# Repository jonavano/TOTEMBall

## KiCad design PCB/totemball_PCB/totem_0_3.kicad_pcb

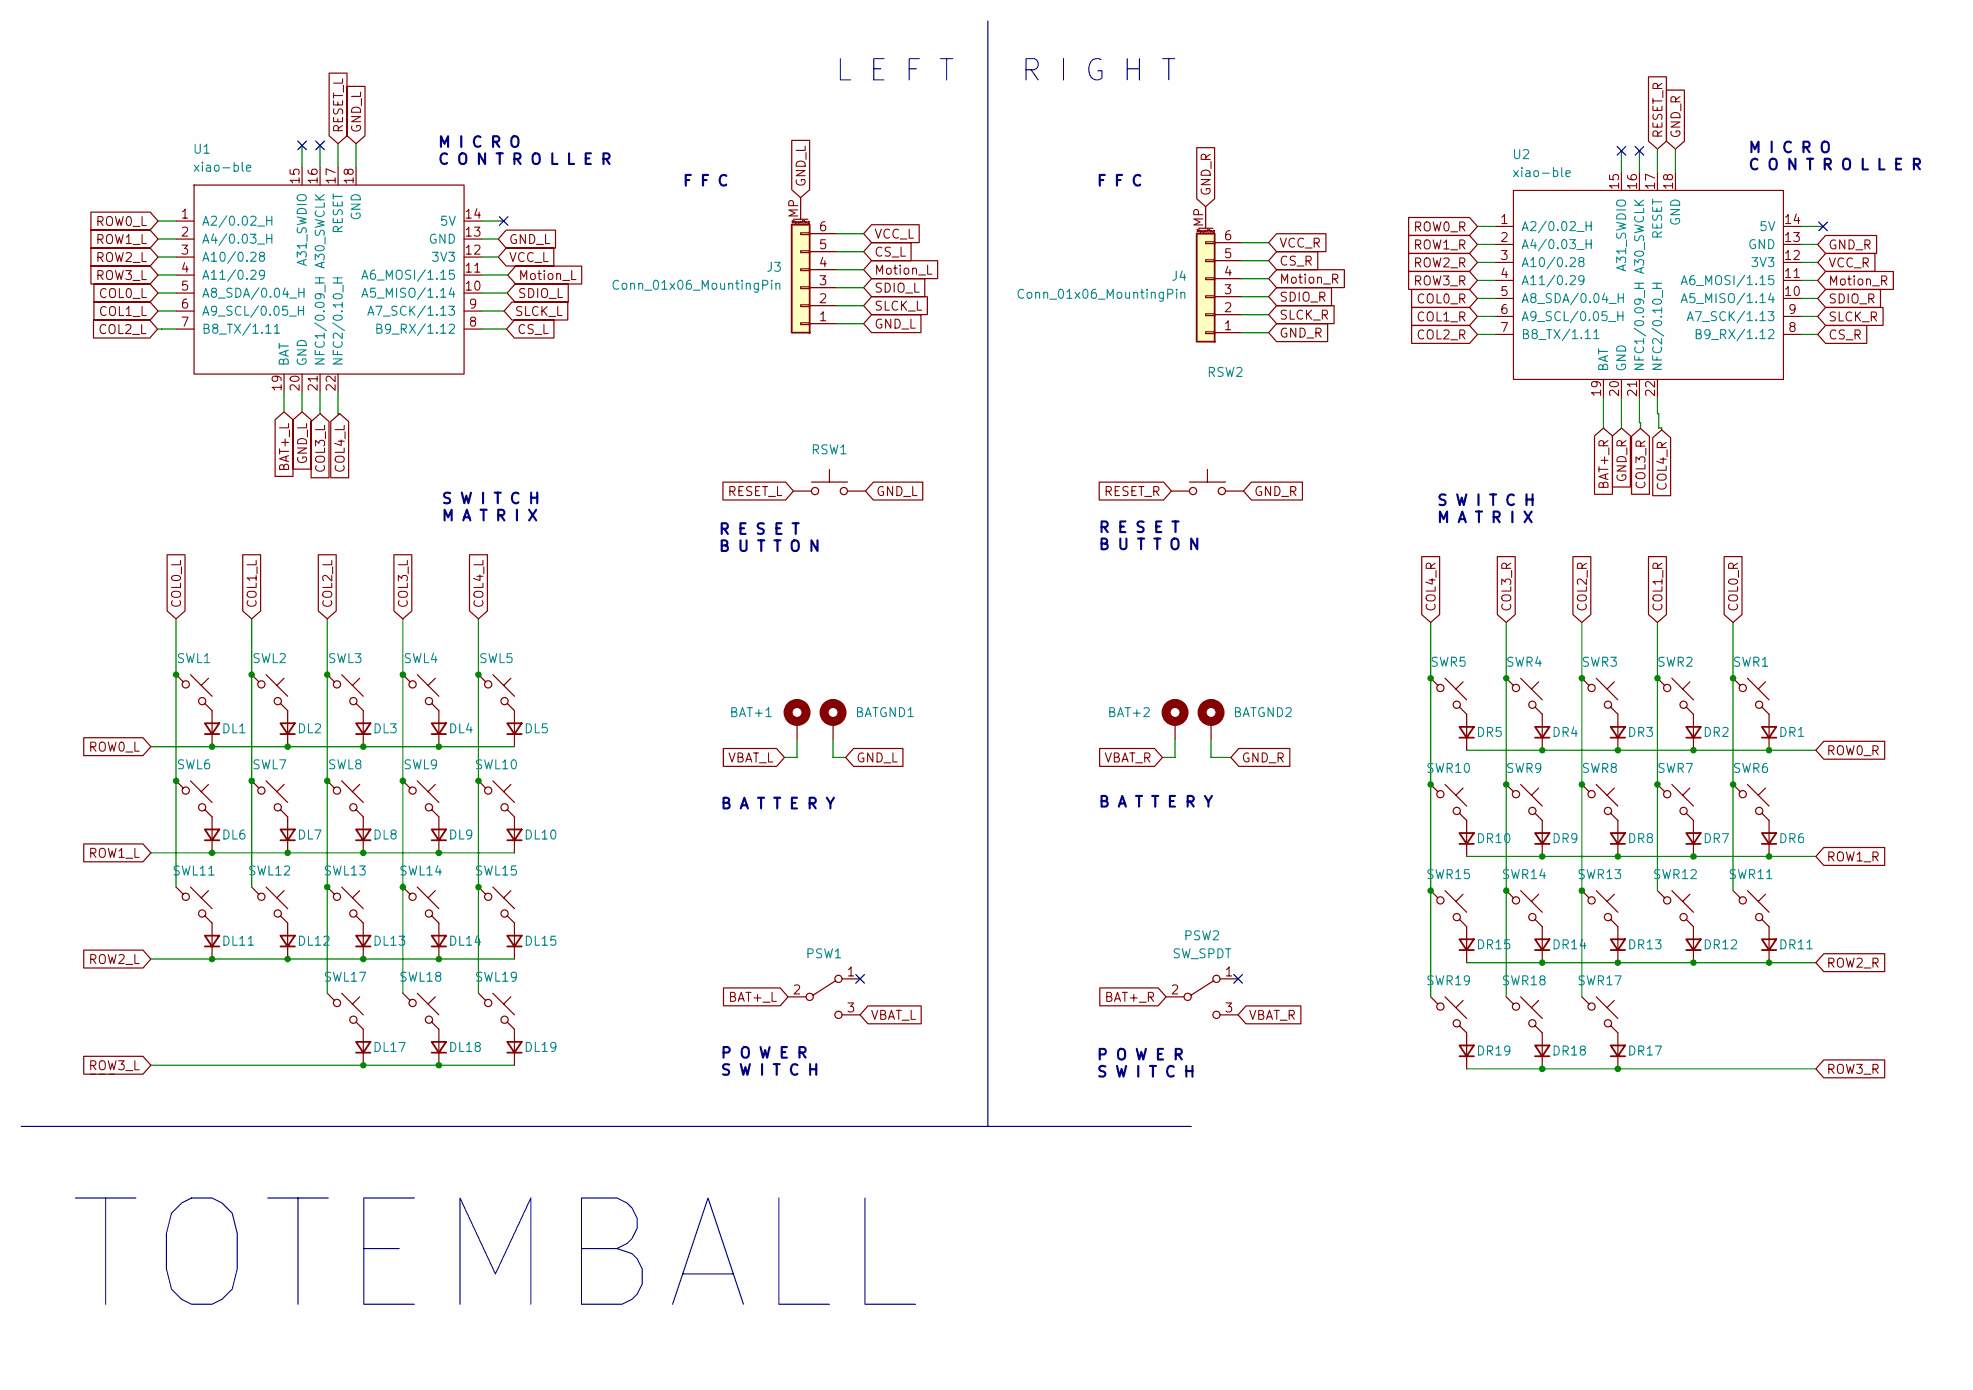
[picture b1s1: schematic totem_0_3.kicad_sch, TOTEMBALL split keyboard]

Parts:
BAT+1, BAT+2: +; BatteryPad
BATGND1, BATGND2: -; BatteryPad
DL1, DL2, DL3, DL4, DL5, DL6, DL7, DL8, DL9, DL10, DL11, DL12, DL13, DL14, DL15, DL17, DL18, DL19: D_Small; Diode_SOD123
DR1, DR2, DR3, DR4, DR5, DR6, DR7, DR8, DR9, DR10, DR11, DR12, DR13, DR14, DR15, DR17, DR18, DR19: D_Small; Diode_SOD123
J3, J4: Conn_01x06_MountingPin; GT-F0501SR10-06S1101
PSW1, PSW2: SW_SPDT; MSK12C02
RSW1, RSW2: SW_Push; SKHLLCA010
SWL1, SWL2, SWL3, SWL4, SWL5, SWL6, SWL7, SWL8, SWL9, SWL10, SWL11, SWL12, SWL13, SWL14, SWL15, SWL17, SWL18, SWL19: SW_Push_45deg; SW_Kailh_Choc_V1V2_HotSwap_Hybrid
SWR1, SWR2, SWR3, SWR4, SWR5, SWR6, SWR7, SWR8, SWR9, SWR10, SWR11, SWR12, SWR13, SWR14, SWR15, SWR17, SWR18, SWR19: SW_Push_45deg; SW_Kailh_Choc_V1V2_HotSwap_Hybrid
U1, U2: xiao-ble; xiao-ble-smd-cutout

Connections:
BAT+_L: PSW1.2 (B), U1.19 (BAT)
BAT+_R: PSW2.2 (B), U2.19 (BAT)
COL0_L: SWL1.1, SWL6.1, SWL11.1, U1.5 (A8_SDA/0.04_H)
COL0_R: SWR1.1, SWR6.1, SWR11.1, U2.5 (A8_SDA/0.04_H)
COL1_L: SWL2.1, SWL7.1, SWL12.1, U1.6 (A9_SCL/0.05_H)
COL1_R: SWR2.1, SWR7.1, SWR12.1, U2.6 (A9_SCL/0.05_H)
COL2_L: SWL3.1, SWL8.1, SWL13.1, SWL17.1, U1.7 (B8_TX/1.11)
COL2_R: SWR3.1, SWR8.1, SWR13.1, SWR17.1, U2.7 (B8_TX/1.11)
COL3_L: SWL4.1, SWL9.1, SWL14.1, SWL18.1, U1.21 (NFC1/0.09_H)
COL3_R: SWR4.1, SWR9.1, SWR14.1, SWR18.1, U2.21 (NFC1/0.09_H)
COL4_L: SWL5.1, SWL10.1, SWL15.1, SWL19.1, U1.22 (NFC2/0.10_H)
COL4_R: SWR5.1, SWR10.1, SWR15.1, SWR19.1, U2.22 (NFC2/0.10_H)
CS_L: J3.5, U1.8 (B9_RX/1.12)
CS_R: J4.5, U2.8 (B9_RX/1.12)
GND_L: BATGND1.1, J3.1, J3.MP (MountPin), RSW1.2, U1.13 (GND), U1.18 (GND), U1.20 (GND)
GND_R: BATGND2.1, J4.1, J4.MP (MountPin), RSW2.2, U2.13 (GND), U2.18 (GND), U2.20 (GND)
Motion_L: J3.4, U1.11 (A6_MOSI/1.15)
Motion_R: J4.4, U2.11 (A6_MOSI/1.15)
unnamed: DL1.2 (A), SWL1.2
unnamed: DL2.2 (A), SWL2.2
unnamed: DL3.2 (A), SWL3.2
unnamed: DL4.2 (A), SWL4.2
unnamed: DL5.2 (A), SWL5.2
unnamed: DL6.2 (A), SWL6.2
unnamed: DL7.2 (A), SWL7.2
unnamed: DL8.2 (A), SWL8.2
unnamed: DL9.2 (A), SWL9.2
unnamed: DL10.2 (A), SWL10.2
unnamed: DL11.2 (A), SWL11.2
unnamed: DL12.2 (A), SWL12.2
unnamed: DL13.2 (A), SWL13.2
unnamed: DL14.2 (A), SWL14.2
unnamed: DL15.2 (A), SWL15.2
unnamed: DL17.2 (A), SWL17.2
unnamed: DL18.2 (A), SWL18.2
unnamed: DL19.2 (A), SWL19.2
unnamed: DR1.2 (A), SWR1.2
unnamed: DR2.2 (A), SWR2.2
unnamed: DR3.2 (A), SWR3.2
unnamed: DR4.2 (A), SWR4.2
unnamed: DR5.2 (A), SWR5.2
unnamed: DR6.2 (A), SWR6.2
unnamed: DR7.2 (A), SWR7.2
unnamed: DR8.2 (A), SWR8.2
unnamed: DR9.2 (A), SWR9.2
unnamed: DR10.2 (A), SWR10.2
unnamed: DR11.2 (A), SWR11.2
unnamed: DR12.2 (A), SWR12.2
unnamed: DR13.2 (A), SWR13.2
unnamed: DR14.2 (A), SWR14.2
unnamed: DR15.2 (A), SWR15.2
unnamed: DR17.2 (A), SWR17.2
unnamed: DR18.2 (A), SWR18.2
unnamed: DR19.2 (A), SWR19.2
RESET_L: RSW1.1, U1.17 (RESET)
RESET_R: RSW2.1, U2.17 (RESET)
ROW0_L: DL1.1 (K), DL2.1 (K), DL3.1 (K), DL4.1 (K), DL5.1 (K), U1.1 (A2/0.02_H)
ROW0_R: DR1.1 (K), DR2.1 (K), DR3.1 (K), DR4.1 (K), DR5.1 (K), U2.1 (A2/0.02_H)
ROW1_L: DL6.1 (K), DL7.1 (K), DL8.1 (K), DL9.1 (K), DL10.1 (K), U1.2 (A4/0.03_H)
ROW1_R: DR6.1 (K), DR7.1 (K), DR8.1 (K), DR9.1 (K), DR10.1 (K), U2.2 (A4/0.03_H)
ROW2_L: DL11.1 (K), DL12.1 (K), DL13.1 (K), DL14.1 (K), DL15.1 (K), U1.3 (A10/0.28)
ROW2_R: DR11.1 (K), DR12.1 (K), DR13.1 (K), DR14.1 (K), DR15.1 (K), U2.3 (A10/0.28)
ROW3_L: DL17.1 (K), DL18.1 (K), DL19.1 (K), U1.4 (A11/0.29)
ROW3_R: DR17.1 (K), DR18.1 (K), DR19.1 (K), U2.4 (A11/0.29)
SDIO_L: J3.3, U1.10 (A5_MISO/1.14)
SDIO_R: J4.3, U2.10 (A5_MISO/1.14)
SLCK_L: J3.2, U1.9 (A7_SCK/1.13)
SLCK_R: J4.2, U2.9 (A7_SCK/1.13)
VBAT_L: BAT+1.1, PSW1.3 (C)
VBAT_R: BAT+2.1, PSW2.3 (C)
VCC_L: J3.6, U1.12 (3V3)
VCC_R: J4.6, U2.12 (3V3)

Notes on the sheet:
M I C R O C O N T R O L L E R
F F C
R E S E T B U T T O N
S W I T C H M A T R I X
P O W E R S W I T C H
TOTEMBALL
B A T T E R Y
R I G H T
L E F T

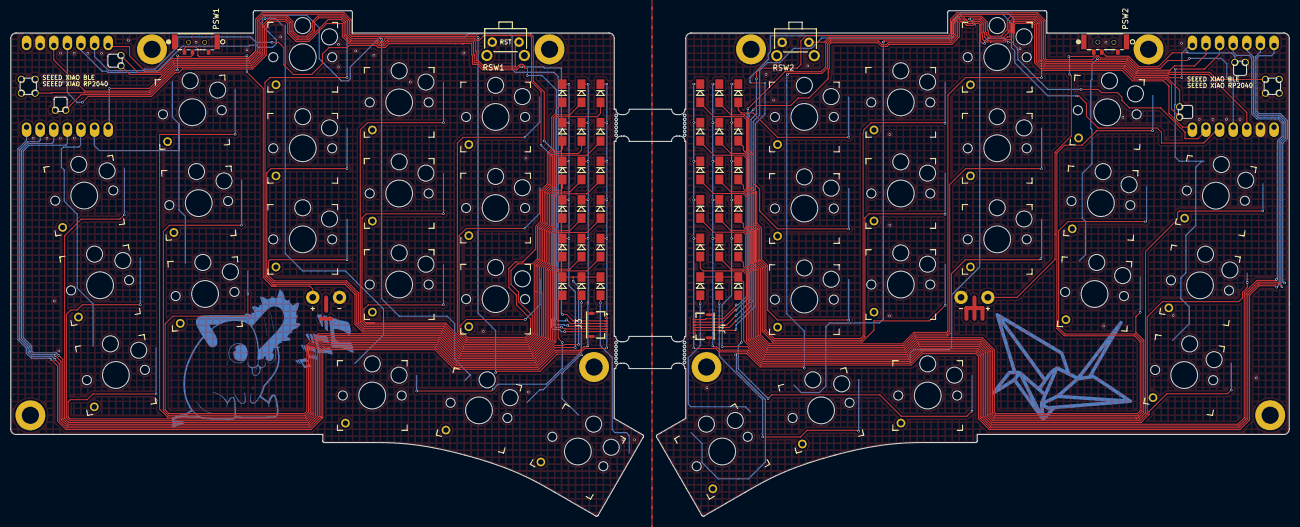
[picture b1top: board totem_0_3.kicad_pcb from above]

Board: 2 copper layers, 238.6 x 94.4 mm, 84 parts (0 on the bottom side), 72 nets.

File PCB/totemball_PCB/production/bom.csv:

Designator,Footprint,Quantity,Value,LCSC Part #
"BAT+1, BAT+2",BatteryPad,2,+,
"BATGND1, BATGND2",BatteryPad,2,-,
"DL1, DL10, DL11, DL12, DL13, DL14, DL15, DL17, DL18, DL19, DL2, DL3, DL4, DL5, DL6, DL7, DL8, DL9, DR1, DR10, DR11, DR12, DR13, DR14, DR15, DR17, DR18, DR19, DR2, DR3, DR4, DR5, DR6, DR7, DR8, DR9",Diode_SOD123,36,D_Small,
"J3, J4",GT-F0501SR10-06S1101,2,Conn_01x06_MountingPin,
"PSW1, PSW2",MSK12C02,2,SW_SPDT,
"RSW1, RSW2",SKHLLCA010,2,SW_Push,
"SWL1, SWL10, SWL11, SWL12, SWL13, SWL14, SWL15, SWL17, SWL18, SWL19, SWL2, SWL3, SWL4, SWL5, SWL6, SWL7, SWL8, SWL9, SWR1, SWR10, SWR11, SWR12, SWR13, SWR14, SWR15, SWR17, SWR18, SWR19, SWR2, SWR3, SWR4, SWR5, SWR6, SWR7, SWR8, SWR9",Kailh_socket_PG1350_optional,36,SW_Push_45deg,
"U1, U2",xiao-ble-smd-cutout,2,xiao-ble,

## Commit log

2025-12-09 small update to pcb and cases
2025-12-09 update schematic
2025-12-09 update xiao footprint
2025-12-09 not working ver, but rewire columns
2025-12-10 moved diodes both sides
2025-12-10 wired right ffc connector
2025-12-10 wired both ffc connectors
2025-12-10 gitignore is now working
2025-12-10 small changes
2025-12-11 set creation of gerber
2025-12-11 socket now supports both v1 and v2 hotswap
2025-12-14 fix errors
2025-12-14 move ffc connector
2025-12-14 update gitignore
2025-12-16 add pochita
